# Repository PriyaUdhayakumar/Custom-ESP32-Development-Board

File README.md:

# Custom ESP32 Development Board

A custom development board based on the ESP32, designed to provide a practical hardware platform for embedded-system development, peripheral interfacing, and PCB design practice.

## Project Overview

This project involves the schematic design and PCB layout of a custom ESP32 development board using **KiCad**.

The objective is to move beyond development boards such as the ESP32 DevKit and design a custom board with the essential circuitry required for ESP32-based embedded applications.

## Features

* ESP32-based custom development board
* Custom schematic design
* Custom PCB layout
* 3.3 V power architecture
* ESP32 power decoupling
* GPIO access for external peripherals
* Programming/debug interface
* Designed using KiCad
* PCB design with practical routing and component placement considerations

## Hardware Design

### Main Controller

* **ESP32**
* 32-bit dual-core microcontroller
* Wi-Fi and Bluetooth connectivity
* Multiple GPIO interfaces
* ADC and other peripheral interfaces

### Power Supply

The board includes the required power circuitry for the ESP32 and its peripherals.

Decoupling capacitors are placed close to the power pins to help reduce supply noise and provide transient current during ESP32 operation.

### PCB Design

The PCB was designed with attention to:

* Component placement
* Signal routing
* Power routing
* Ground connectivity
* Decoupling capacitor placement
* Trace-width selection
* Design Rule Check (DRC)

## Design Tool

**KiCad**

The project includes:

```text
├── Schematic
│   └── Custom ESP32 Development Board schematic
│
└── PCB
    └── Custom ESP32 Development Board PCB layout
```

## Repository Contents

| File                  | Description      |
| --------------------- | ---------------- |
| `esp32 (1).kicad_sch` | KiCad schematic  |
| `esp32 (1).kicad_pcb` | KiCad PCB layout |

## Learning Objectives

This project was developed to strengthen practical skills in:

* Embedded hardware design
* ESP32 hardware interfacing
* Circuit schematic design
* PCB layout
* Component placement
* PCB routing
* Power and decoupling design
* KiCad
* Hardware debugging and design validation

## Project Status

**Hardware design:** In progress / under development

The schematic and PCB design have been created in KiCad. Further hardware validation and testing will be performed after PCB fabrication and assembly.

## Future Improvements

* PCB fabrication and assembly
* Hardware bring-up and testing
* Verify all power rails
* Test ESP32 programming and debugging
* Test GPIO and peripheral interfaces
* Add project photographs and PCB 3D views
* Document hardware validation results

## Author

**Priya Udhayakumar**

Electronics & Communication Engineer
Focused on Embedded Systems and PCB Design

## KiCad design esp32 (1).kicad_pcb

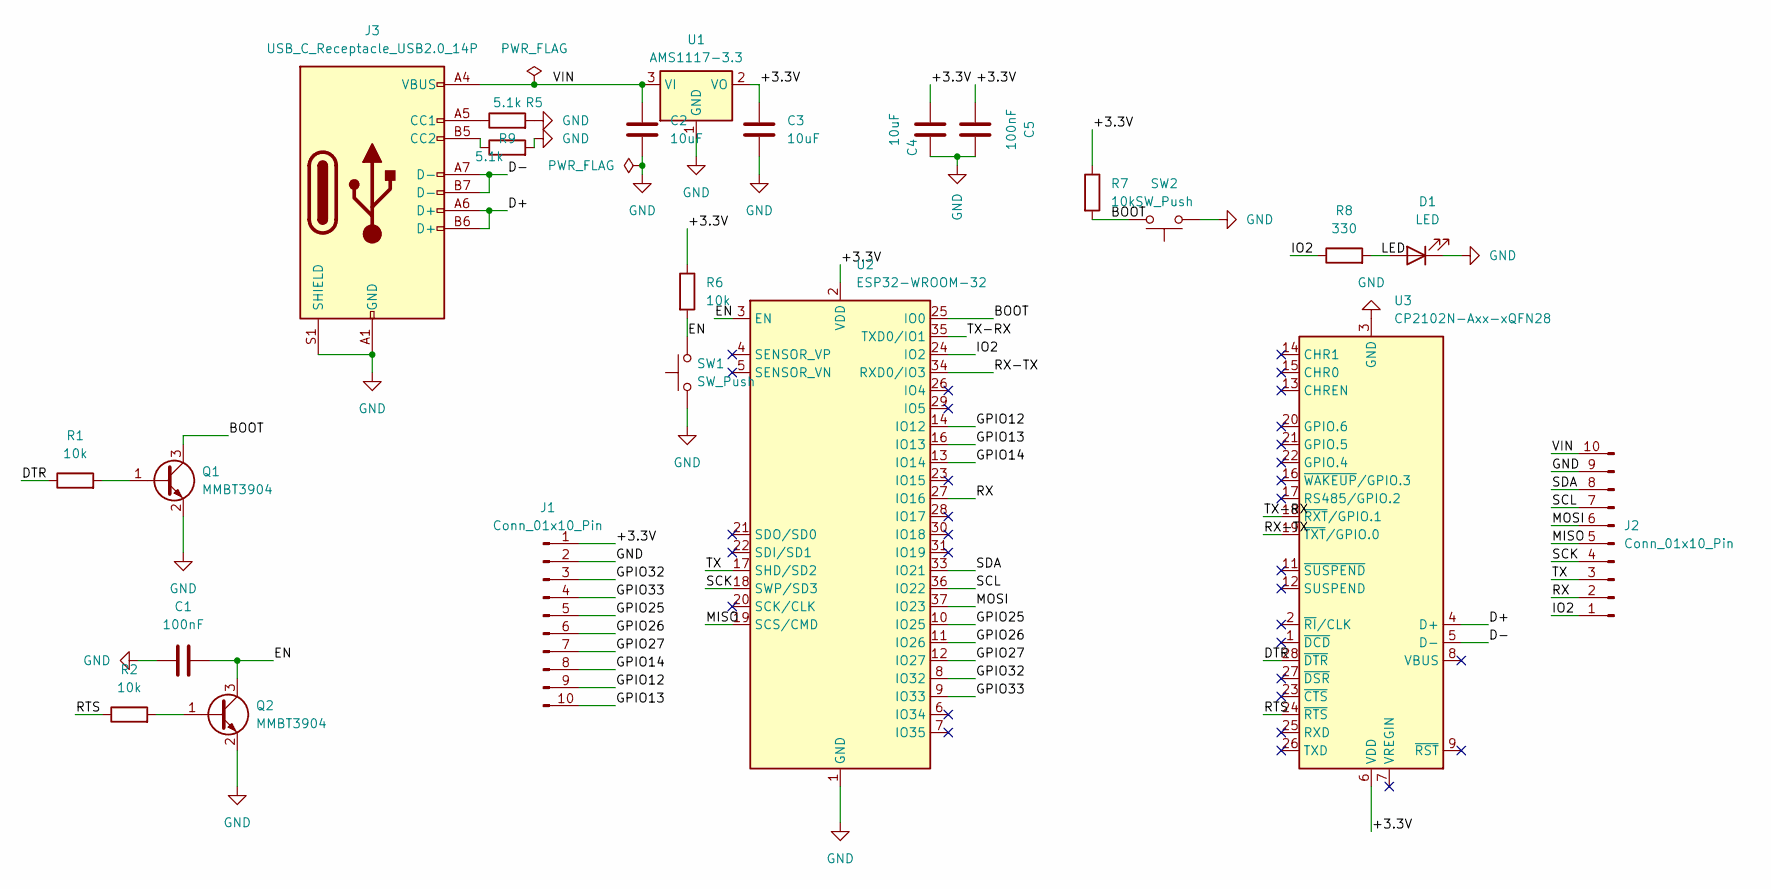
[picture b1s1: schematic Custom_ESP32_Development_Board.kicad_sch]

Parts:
C1, C5: 100nF; C_0805_2012Metric
C2, C3, C4: 10uF; C_0805_2012Metric
D1: LED; LED_0603_1608Metric
J1, J2: Conn_01x10_Pin; PinHeader_1x10_P2.54mm_Vertical
J3: USB_C_Receptacle_USB2.0_14P; USB_C_Receptacle_HRO_TYPE-C-31-M-12
Q1, Q2: MMBT3904; SOT-23
R1, R2, R6, R7: 10k; R_0805_2012Metric
R5, R9: 5.1k; R_0805_2012Metric
R8: 330; R_0805_2012Metric
SW1, SW2: SW_Push; SW_Push_1P1T_NO_CK_KMR2
U1: AMS1117-3.3; SOT-223-3_TabPin2
U2: ESP32-WROOM-32
U3: CP2102N-Axx-xQFN28; QFN-28-1EP_5x5mm_P0.5mm_EP3.35x3.35mm

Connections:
/+3.3V: C3.1, C4.2, C5.2, J1.1, R6.1, R7.1, U1.2 (VO), U2.2 (VDD), U3.6 (VDD)
/BOOT: Q1.3 (C), R7.2, SW2.2, U2.25 (IO0)
/D+: J3.A6 (D+), J3.B6 (D+), U3.4 (D+)
/D-: J3.A7 (D-), J3.B7 (D-), U3.5 (D-)
/DTR: R1.1, U3.28 (~DTR)
/EN: C1.2, Q2.3 (C), R6.2, SW1.2, U2.3 (EN)
/GPIO12: J1.9, U2.14 (IO12)
/GPIO13: J1.10, U2.16 (IO13)
/GPIO14: J1.8, U2.13 (IO14)
/GPIO25: J1.5, U2.10 (IO25)
/GPIO26: J1.6, U2.11 (IO26)
/GPIO27: J1.7, U2.12 (IO27)
/GPIO32: J1.3, U2.8 (IO32)
/GPIO33: J1.4, U2.9 (IO33)
/IO2: J2.1, R8.1, U2.24 (IO2)
/LED: D1.2 (A), R8.2
/MISO: J2.5, U2.19 (SCS/CMD)
/MOSI: J2.6, U2.37 (IO23)
/RTS: R2.1, U3.24 (~RTS)
/RX: J2.2, U2.27 (IO16)
/RX-TX: U2.34 (RXD0/IO3), U3.19 (~TXT/GPIO.0)
/SCK: J2.4, U2.18 (SWP/SD3)
/SCL: J2.7, U2.36 (IO22)
/SDA: J2.8, U2.33 (IO21)
/TX: J2.3, U2.17 (SHD/SD2)
/TX-RX: U2.35 (TXD0/IO1), U3.18 (~RXT/GPIO.1)
/VIN: C2.1, J2.10, J3.A4 (VBUS), J3.A9 (VBUS), J3.B4 (VBUS), J3.B9 (VBUS), U1.3 (VI)
GND: C1.1, C2.2, C3.2, C4.1, C5.1, D1.1 (K), J1.2, J2.9, J3.A1 (GND), J3.A12 (GND), J3.B1 (GND), J3.B12 (GND), J3.S1 (SHIELD), Q1.2 (E), Q2.2 (E), R5.2, R9.2, SW1.1, SW2.1, U1.1 (GND), U2.1 (GND), U2.15 (GND), U2.38 (GND), U2.39 (GND), U3.3 (GND), U3.29 (GND)
unnamed: J3.A5 (CC1), R5.1
unnamed: J3.B5 (CC2), R9.1
unnamed: Q1.1 (B), R1.2
unnamed: Q2.1 (B), R2.2

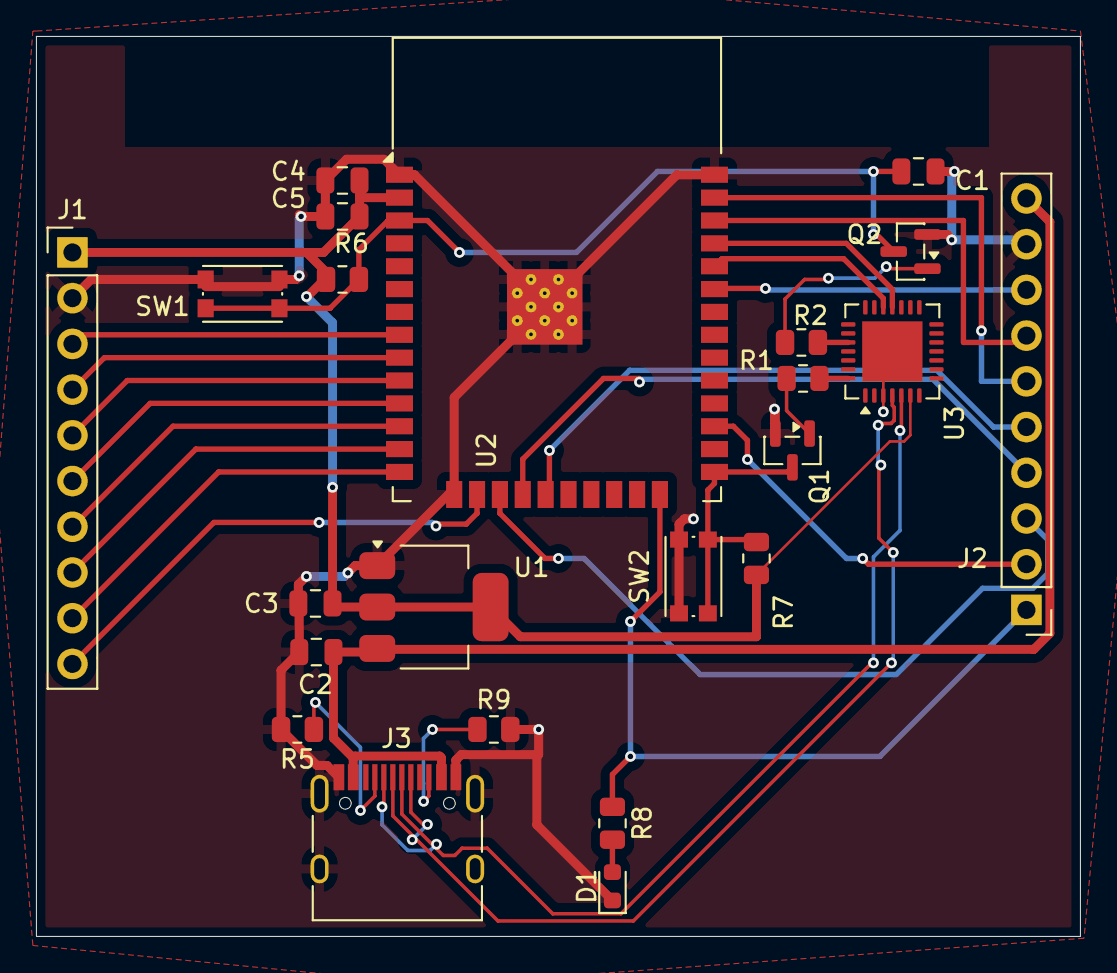
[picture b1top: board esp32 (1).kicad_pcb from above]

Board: 2 copper layers, 58.0 x 50.0 mm, 23 parts (0 on the bottom side), 32 nets.
